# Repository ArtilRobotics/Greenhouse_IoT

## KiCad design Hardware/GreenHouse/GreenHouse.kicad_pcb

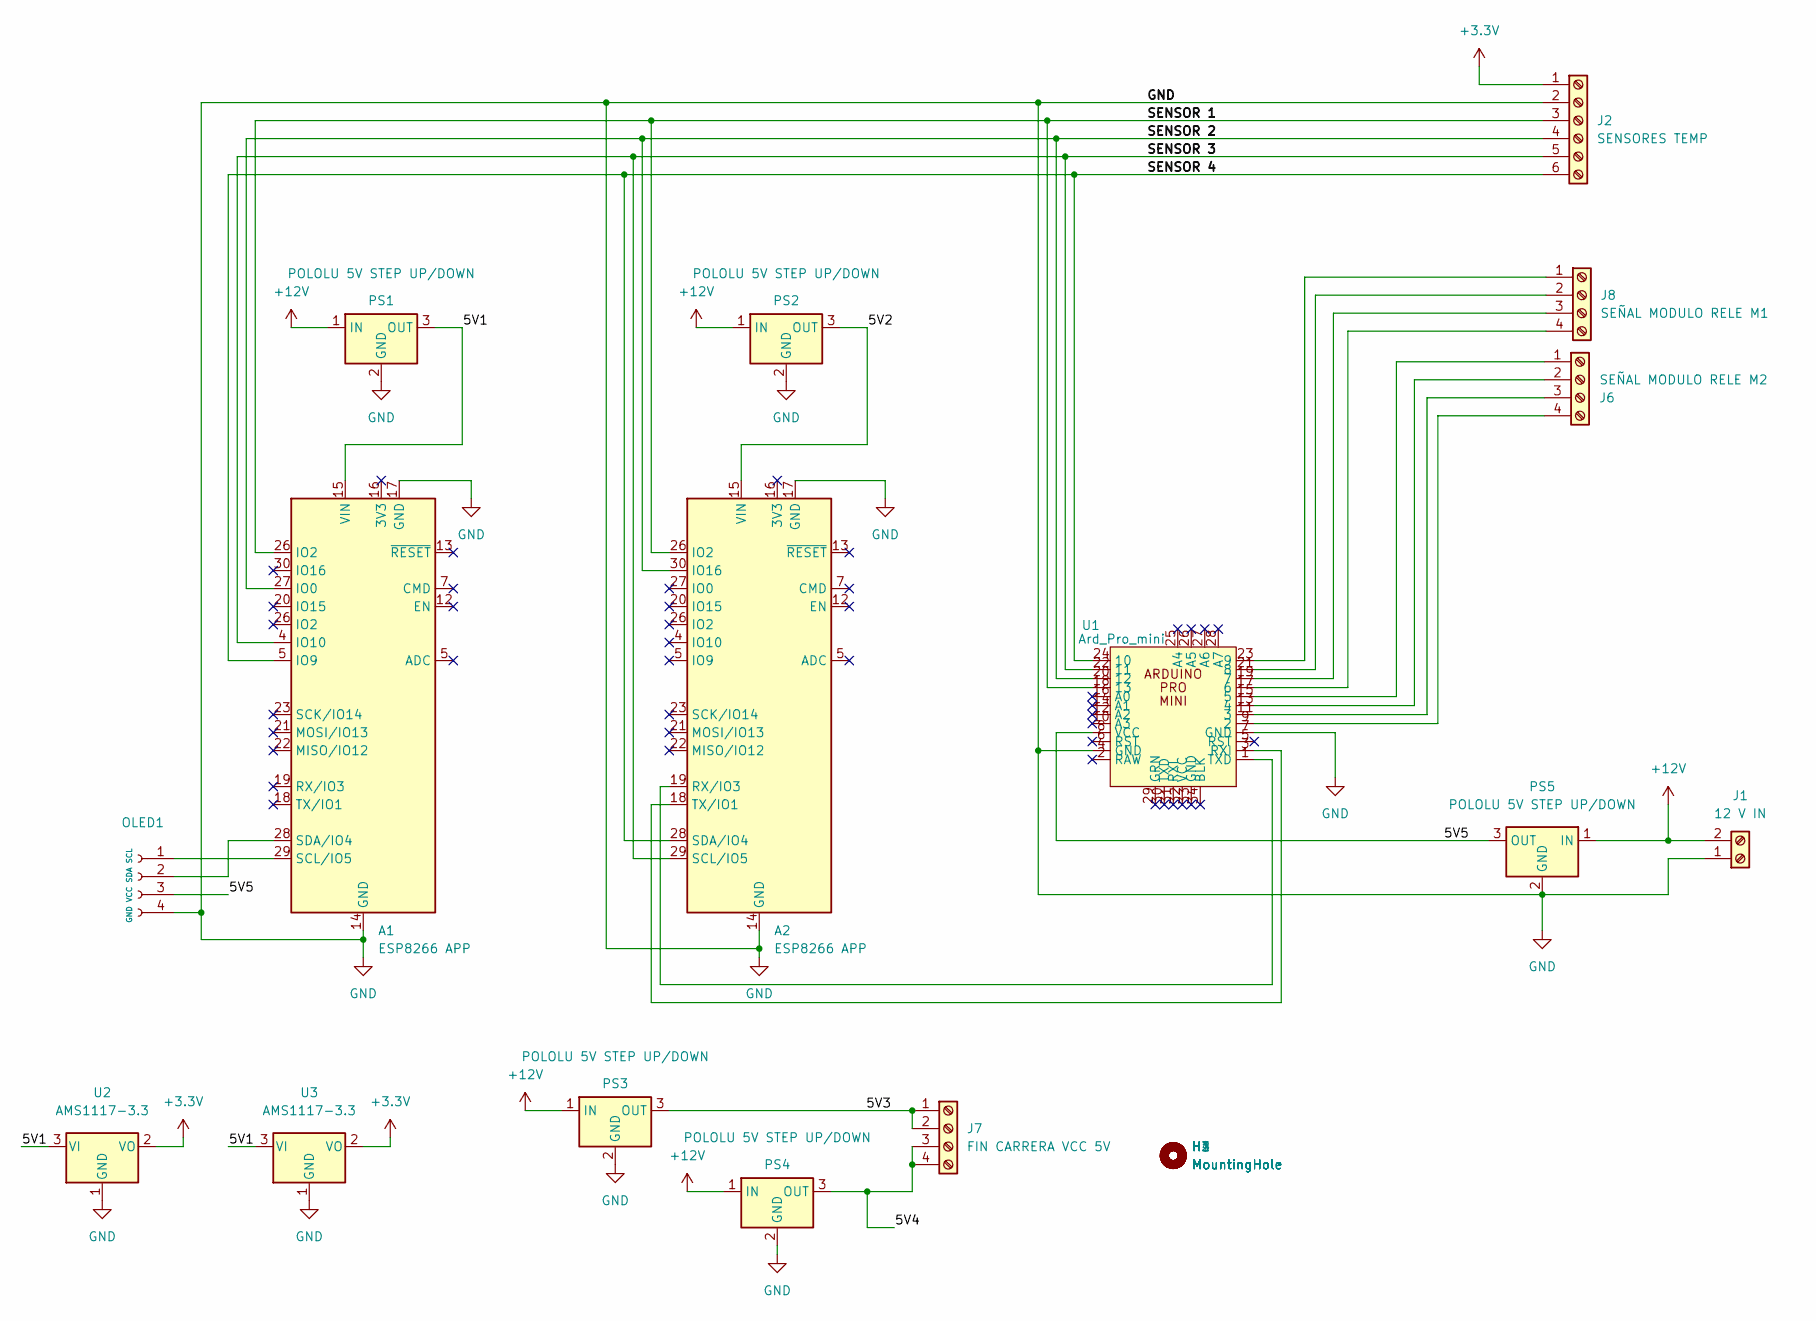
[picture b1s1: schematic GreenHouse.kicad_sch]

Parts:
A1, A2: ESP8266 APP; ESP12F-Devkit-V3
H1, H2, H3, H4: MountingHole; MountingHole_3.2mm_M3
J1: 12 V IN; TerminalBlock_bornier-2_P5.08mm
J2: SENSORES TEMP; TerminalBlock_bornier-6_P5.08mm
J6: SEÑAL MODULO RELE M2; TerminalBlock_bornier-4_P5.08mm
J7: FIN CARRERA VCC 5V; TerminalBlock_bornier-4_P5.08mm
J8: SEÑAL MODULO RELE M1; TerminalBlock_bornier-4_P5.08mm
OLED1: GND VCC SDA SCL; PinHeader_1x04_P2.54mm_Vertical
PS1, PS2, PS3, PS4, PS5: POLOLU 5V STEP UP/DOWN; Converter_DCDC_Murata_OKI-78SR_Horizontal
U1: Ard_Pro_mini; Arduino_Pro_Mini
U2, U3: AMS1117-3.3; SOT-223-3_TabPin2

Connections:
+3.3V: J2.1, U2.2 (VO), U3.2 (VO)
+12V: J1.2, PS1.1 (IN), PS2.1 (IN), PS3.1 (IN), PS4.1 (IN), PS5.1 (IN)
/5V1: A1.15 (VIN), PS1.3 (OUT), U2.3 (VI), U3.3 (VI)
/5V2: A2.15 (VIN), PS2.3 (OUT)
/5V3: J7.1, J7.2, PS3.3 (OUT)
/5V4: J7.3, J7.4, PS4.3 (OUT)
/5V5: OLED1.3, PS5.3 (OUT), U1.8 (VCC)
/SENSOR 1: A1.26 (IO2), A2.26 (IO2), J2.3, U1.18 (13)
/SENSOR 2: A1.27 (IO0), A2.30 (IO16), J2.4, U1.20 (12)
/SENSOR 3: A1.4 (IO10), A2.29 (SCL/IO5), J2.5, U1.22 (11)
/SENSOR 4: A1.5 (IO9), A2.28 (SDA/IO4), J2.6, U1.24 (10)
GND: A1.14 (GND), A1.17 (GND), A2.14 (GND), A2.17 (GND), J1.1, J2.2, OLED1.4, PS1.2 (GND), PS2.2 (GND), PS3.2 (GND), PS4.2 (GND), PS5.2 (GND), U1.4 (GND), U1.7 (GND), U2.1 (GND), U3.1 (GND)
unnamed: A1.28 (SDA/IO4), OLED1.2
unnamed: A1.29 (SCL/IO5), OLED1.1
unnamed: A2.18 (TX/IO1), U1.3 (RXI)
unnamed: A2.19 (RX/IO3), U1.1 (TXD)
unnamed: J6.1, U1.15 (5)
unnamed: J6.2, U1.13 (4)
unnamed: J6.3, U1.11 (3)
unnamed: J6.4, U1.9 (2)
unnamed: J8.1, U1.23 (9)
unnamed: J8.2, U1.21 (8)
unnamed: J8.3, U1.19 (7)
unnamed: J8.4, U1.17 (6)

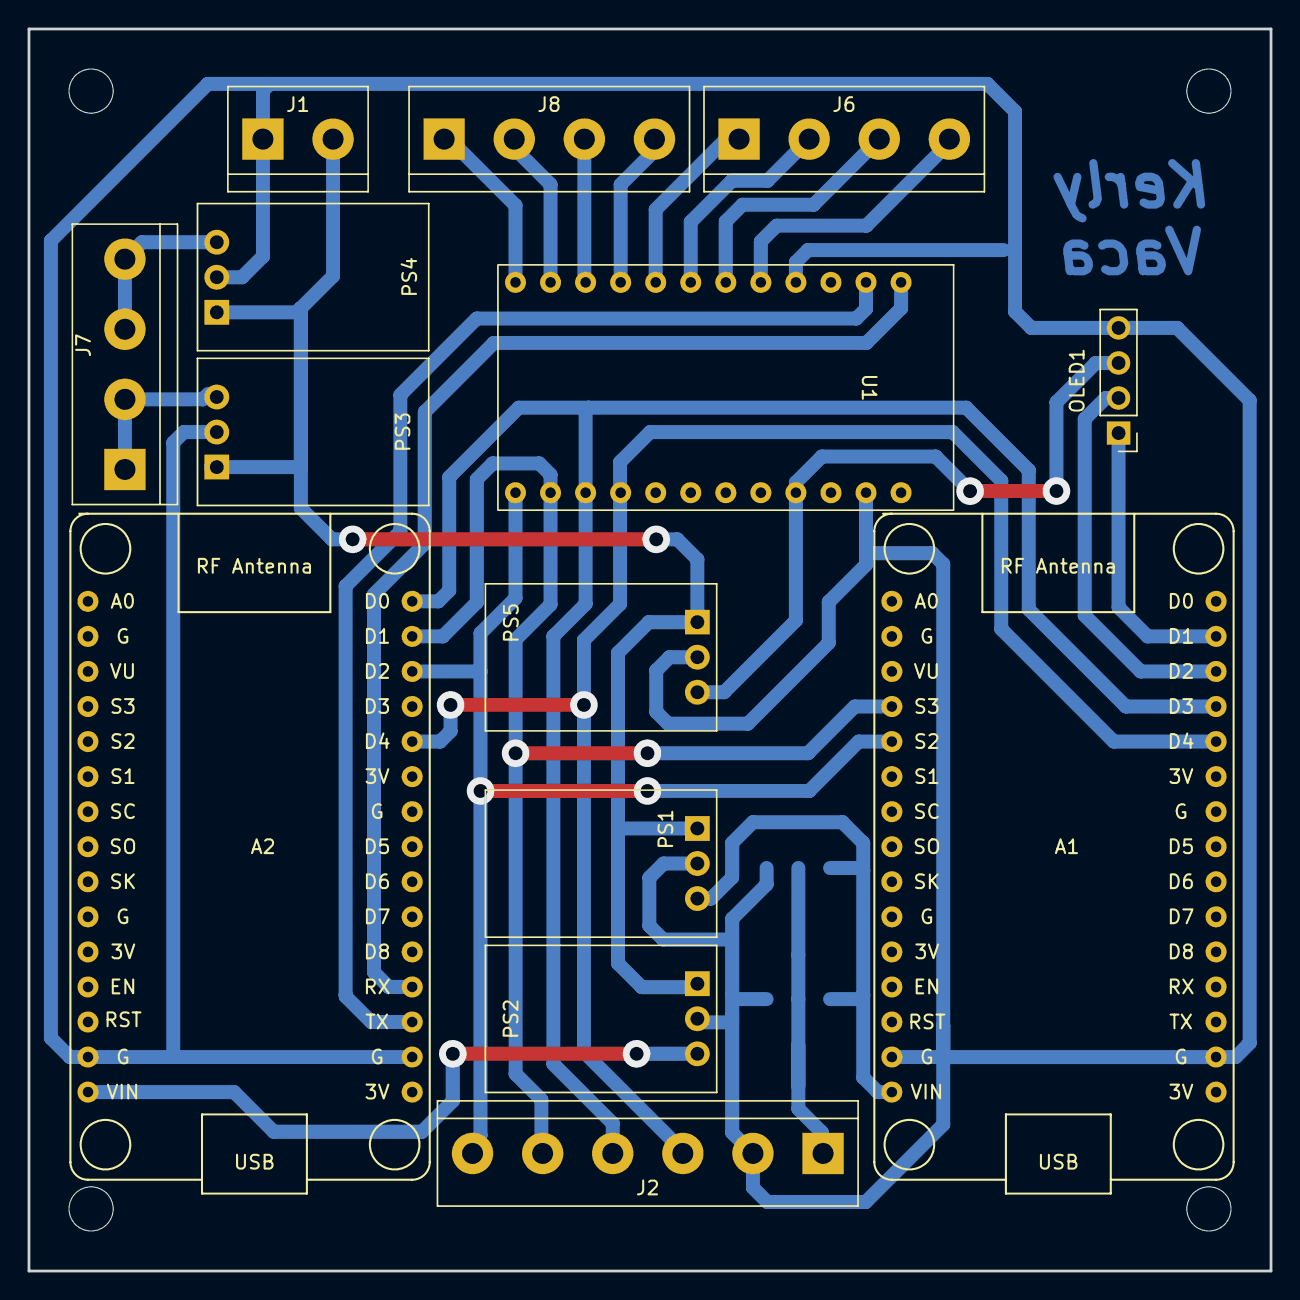
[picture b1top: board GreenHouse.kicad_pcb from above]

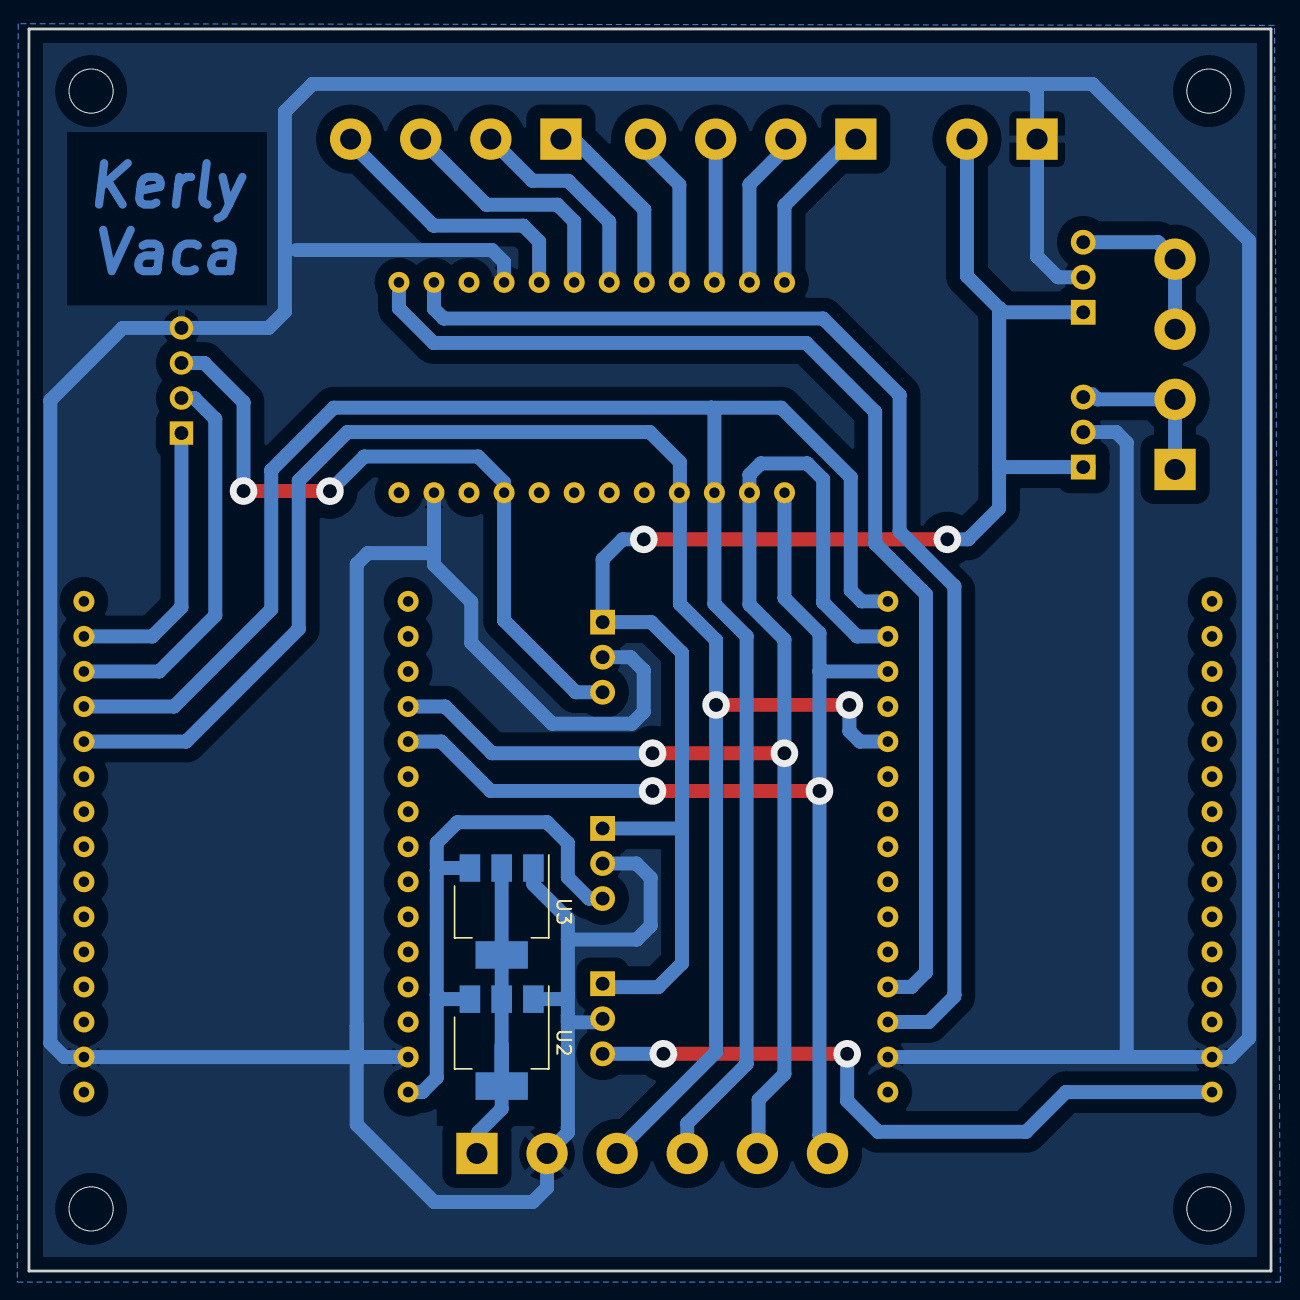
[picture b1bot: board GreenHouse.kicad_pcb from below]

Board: 2 copper layers, 90.0 x 90.0 mm, 20 parts (2 on the bottom side), 24 nets.

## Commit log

2023-02-01 feat!: Placa Dev Modules
2023-02-02 fix: reduce the board size & re trace some parts.
2023-02-13 docs: add Boom in Html
